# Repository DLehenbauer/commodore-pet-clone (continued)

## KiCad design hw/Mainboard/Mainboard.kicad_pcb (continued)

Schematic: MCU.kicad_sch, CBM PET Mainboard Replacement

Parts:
C68, C69, C81: 2.2u 6.3V; C_0402_1005Metric; LCSC C12530
C70, C71, C72, C73, C74, C75, C76, C77: 100n; C_0402_1005Metric; LCSC C307331
C78, C79: 30p; C_0402_1005Metric; LCSC C1570
C80: 10u; C_0603_1608Metric; LCSC C96446
D14: LED_GRN; LED_0603_1608Metric; LCSC C72043
J22: MENU; PinHeader_1x02_P2.54mm_Vertical; MOUSER 649-1012937893602BLF
JP8: DVI_CEC; SolderJumper-2_P1.3mm_Open_RoundedPad1.0x1.5mm
JP9: DVI_SDA; SolderJumper-3_P1.3mm_Open_RoundedPad1.0x1.5mm
JP10: DVI_SCL; SolderJumper-3_P1.3mm_Open_RoundedPad1.0x1.5mm
PT47, PT48: PowerTie_2; NetTie-2_SMD_Pad_1.6_to_0.4mm
R38, R39: 27; R_0603_1608Metric; LCSC C25190
R40, R41, R52, R53: 2k2; R_0402_1005Metric; LCSC C25879
R42, R43, R44, R45, R46, R47, R48: 33; R_0402_1005Metric; LCSC C25105
R49, R51, R55: 1k; R_0402_1005Metric; LCSC C11702
R50: 15k; R_0402_1005Metric; LCSC C25756
R54: 10k; R_0402_1005Metric; LCSC C25744
SW4: RUN; SW-TH_L6.0-W3.5-P6.50; MOUSER 611-PTS636SK43LFS
SW5: MENU; APEM_MJTP1117; MOUSER 642-MJTP1117
U21: RP2040; LQFN-56_L7.0-W7.0-P0.4-EP; LCSC C2040
Y1: 12 MHz; Crystal_SMD_3225-4Pin_3.2x2.5mm; LCSC C9002

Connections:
+3V3: PT47.1, R40.1, R41.1, R50.1, R52.1, R53.1; also elsewhere on the board
/MAGIC/FPGA/CEC: JP8.1 (A), U21.36 (GPIO24); also elsewhere on the board
/MAGIC/FPGA/FPGA_CLK: R48.1; also elsewhere on the board
/MAGIC/FPGA/I2C0_SCL: JP10.1 (A), R53.2; also elsewhere on the board
/MAGIC/FPGA/I2C0_SDA: JP9.1 (A), R52.2; also elsewhere on the board
/MAGIC/FPGA/I2C1_SCL: R41.2, U21.5 (GPIO3); also elsewhere on the board
/MAGIC/FPGA/I2C1_SDA: R40.2, U21.4 (GPIO2); also elsewhere on the board
/MAGIC/FPGA/SPI0_RX: U21.6 (GPIO4); also elsewhere on the board
/MAGIC/FPGA/SPI0_SCK: R43.1; also elsewhere on the board
/MAGIC/FPGA/SPI0_TX: R44.1; also elsewhere on the board
/MAGIC/FPGA/SPI0_~CS: R42.1; also elsewhere on the board
/MAGIC/FPGA/SPI1_RX: U21.15 (GPIO12); also elsewhere on the board
/MAGIC/FPGA/SPI1_SCK: R47.1; also elsewhere on the board
/MAGIC/FPGA/SPI1_TX: R45.1; also elsewhere on the board
/MAGIC/FPGA/SPI1_~CS: R46.1; also elsewhere on the board
/MAGIC/FPGA/SPI1_~READY: U21.13 (GPIO10); also elsewhere on the board
/MAGIC/FPGA/SWCLK: U21.24 (SWCLK); also elsewhere on the board
/MAGIC/FPGA/SWD: U21.25 (SWD); also elsewhere on the board
/MAGIC/FPGA/UART_RX: U21.3 (GPIO1); also elsewhere on the board
/MAGIC/FPGA/UART_TX: U21.2 (GPIO0); also elsewhere on the board
/MAGIC/FPGA/~CRESET: R54.2; also elsewhere on the board
/MAGIC/FPGA/~SPI_ENA: R50.2, R51.2, U21.26 (RUN); also elsewhere on the board
/MAGIC/MCU/DVDD: C68.1, C70.1, C71.1, U21.23 (DVDD), U21.45 (VREG_VOUT), U21.50 (DVDD)
/MAGIC/MCU/DVI/CEC: JP8.2 (B); also elsewhere on the board
/MAGIC/MCU/DVI/DVI_CK+: U21.28 (GPIO17); also elsewhere on the board
/MAGIC/MCU/DVI/DVI_CK-: U21.27 (GPIO16); also elsewhere on the board
/MAGIC/MCU/DVI/DVI_D0+: U21.30 (GPIO19); also elsewhere on the board
/MAGIC/MCU/DVI/DVI_D0-: U21.29 (GPIO18); also elsewhere on the board
/MAGIC/MCU/DVI/DVI_D1+: U21.32 (GPIO21); also elsewhere on the board
/MAGIC/MCU/DVI/DVI_D1-: U21.31 (GPIO20); also elsewhere on the board
/MAGIC/MCU/DVI/DVI_D2+: U21.35 (GPIO23); also elsewhere on the board
/MAGIC/MCU/DVI/DVI_D2-: U21.34 (GPIO22); also elsewhere on the board
/MAGIC/MCU/DVI/SCL: JP10.3 (B); also elsewhere on the board
/MAGIC/MCU/DVI/SDA: JP9.3 (B); also elsewhere on the board
/MAGIC/MCU/Flash/SCK: U21.52 (QSPI_SCLK); also elsewhere on the board
/MAGIC/MCU/Flash/SD0: U21.53 (QSPI_SD0); also elsewhere on the board
/MAGIC/MCU/Flash/SD1: U21.55 (QSPI_SD1); also elsewhere on the board
/MAGIC/MCU/Flash/SD2: U21.54 (QSPI_SD2); also elsewhere on the board
/MAGIC/MCU/Flash/SD3: U21.51 (QSPI_SD3); also elsewhere on the board
/MAGIC/MCU/Flash/~CS: U21.56 (QSPI_SS); also elsewhere on the board
/MAGIC/MCU/GP25: R55.1, U21.37 (GPIO25)
/MAGIC/MCU/GP27: C81.1, J22.2, SW5.2, U21.39 (GPIO27_ADC1)
/MAGIC/MCU/MCU_FPGA_CLK: R48.2, U21.18 (GPIO15)
/MAGIC/MCU/MCU_I2C0_SCL: JP10.2 (C), U21.41 (GPIO29_ADC3)
/MAGIC/MCU/MCU_I2C0_SDA: JP9.2 (C), U21.40 (GPIO28_ADC2)
/MAGIC/MCU/MCU_SPI0_SCK: R43.2, U21.8 (GPIO6)
/MAGIC/MCU/MCU_SPI0_TX: R44.2, U21.9 (GPIO7)
/MAGIC/MCU/MCU_SPI0_~CS: R42.2, U21.7 (GPIO5)
/MAGIC/MCU/MCU_SPI1_SCK: R47.2, U21.17 (GPIO14)
/MAGIC/MCU/MCU_SPI1_TX: R45.2, U21.14 (GPIO11)
/MAGIC/MCU/MCU_SPI1_~CS: R46.2, U21.16 (GPIO13)
/MAGIC/MCU/MCU_TESTEN: PT48.2, U21.19 (TESTEN)
/MAGIC/MCU/MCU_USB_D+: R38.1, U21.47 (USB_DP)
/MAGIC/MCU/MCU_USB_D-: R39.1, U21.46 (USB_DM)
/MAGIC/MCU/MCU_~CRESET: R54.1, U21.38 (GPIO26_ADC0)
/MAGIC/MCU/SD_DETECT: U21.11 (GPIO8); also elsewhere on the board
/MAGIC/MCU/SD_~CS: U21.12 (GPIO9); also elsewhere on the board
/MAGIC/MCU/USB/USB_D+: R38.2; also elsewhere on the board
/MAGIC/MCU/USB/USB_D-: R39.2; also elsewhere on the board
/MAGIC/MCU/XIN: C78.2, U21.20 (XIN), Y1.1
/MAGIC/MCU/XOUT: R49.2, U21.21 (XOUT)
GND: C68.2, C69.2, C70.2, C71.2, C72.2, C73.2, C74.2, C75.2, C76.2, C77.2, C78.1, C79.1, C80.2, C81.2, D14.1 (K), J22.1, PT48.1, SW5.1, U21.57 (GND), Y1.2, Y1.4; also elsewhere on the board
MCU_IOVDD: C69.1, C72.1, C73.1, C74.1, C75.1, C76.1, C77.1, PT47.2, U21.1 (IOVDD), U21.10 (IOVDD), U21.22 (IOVDD), U21.33 (IOVDD), U21.42 (IOVDD), U21.43 (ADC_AVDD), U21.44 (VREG_IN), U21.48 (USB_VDD), U21.49 (IOVDD)
unnamed: C79.2, R49.1, Y1.3
unnamed: C80.1, R51.1, SW4.2
unnamed: D14.2 (A), R55.2
PD_GND: SW4.1; also elsewhere on the board

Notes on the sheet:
IO/USB/AVDD Decoupling
~{SPI_ENA} is driven low during FPGA programming. We use this to hold the MCU in reset when updating the FPGA to avoid contention on SPI pins. FT2232H can source/sink ~8ma, so 1K should be ok.
DVDD Decoupling
10k resistor on ~{CRESET} enables programmer to override MCU during development.

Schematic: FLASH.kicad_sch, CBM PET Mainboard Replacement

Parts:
C85: 100n; C_0402_1005Metric; LCSC C307331
R72: 10k; R_0402_1005Metric; LCSC C25744
R73: 1k; R_0402_1005Metric; LCSC C11702
SW6: BOOTSEL; SW-TH_L6.0-W3.5-P6.50; MOUSER 611-PTS636SK43LFS
U22: W25Q128JVS; SOIC-8_5.23x5.23mm_P1.27mm; LCSC C97521

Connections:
+3V3: C85.1, R72.1, U22.8 (VCC); also elsewhere on the board
/MAGIC/MCU/Flash/SCK: U22.6 (CLK); also elsewhere on the board
/MAGIC/MCU/Flash/SD0: U22.5 (DI(IO0)); also elsewhere on the board
/MAGIC/MCU/Flash/SD1: U22.2 (DO(IO1)); also elsewhere on the board
/MAGIC/MCU/Flash/SD2: U22.3 (IO2); also elsewhere on the board
/MAGIC/MCU/Flash/SD3: U22.7 (IO3); also elsewhere on the board
/MAGIC/MCU/Flash/~CS: R72.2, R73.2, U22.1 (~CS); also elsewhere on the board
GND: C85.2, SW6.1, U22.4 (GND); also elsewhere on the board
unnamed: R73.1, SW6.2

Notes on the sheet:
Flash

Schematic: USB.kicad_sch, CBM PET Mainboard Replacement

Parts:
C84: 4.7u 16V; C_0603_1608Metric; LCSC C19666
J25: USB2.0_HOST_TYPE_C; USB-C_SMD-TYPE-C-31-M-12; LCSC C165948
PT51, PT52, PT53, PT54: PowerTie_2; NetTie-2_SMD_Pad_1.6_to_0.4mm
R70, R71: 56k; R_0402_1005Metric; LCSC C25796

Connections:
+5V: C84.1, PT51.1, PT52.1; also elsewhere on the board
/MAGIC/MCU/USB/CC1: J25.A5 (CC1), R70.2
/MAGIC/MCU/USB/CC2: J25.B5 (CC2), R71.2
/MAGIC/MCU/USB/USB_D+: J25.A6 (D+), J25.B6 (D+); also elsewhere on the board
/MAGIC/MCU/USB/USB_D-: J25.A7 (D-), J25.B7 (D-); also elsewhere on the board
/MAGIC/MCU/USB/VBUS1: J25.A4_B9 (VBUS), PT51.2, R70.1
/MAGIC/MCU/USB/VBUS2: J25.A9_B4 (VBUS), PT52.2, R71.1
GND: J25.S1 (SHIELD); also elsewhere on the board
unnamed: J25.A1_B12 (GND), PT54.2
unnamed: J25.A12_B1 (GND), PT53.2
PD_GND: C84.2, PT53.1, PT54.1; also elsewhere on the board

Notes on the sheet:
USB 2.0 Host over USB-C connector The 56k pullups on CC1 and CC2 identify as a downstream facing port supplying 5V @ 900ma.

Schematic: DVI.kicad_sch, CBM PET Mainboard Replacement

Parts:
J23: NOT_HDMI_A; HDMI_A_Molex_208658-1001_Horizontal; LCSC C138388
PT49, PT50: PowerTie_2; NetTie-2_SMD_Pad_1.6_to_0.4mm
R56, R57, R58, R59, R60, R61, R65, R66, R67: 270; R_0603_1608Metric; LCSC C22966
R62, R63, R64: 2k2; R_0402_1005Metric; LCSC C25879

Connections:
+3V3: R62.1; also elsewhere on the board
+5V: PT49.1; also elsewhere on the board
/MAGIC/MCU/DVI/CEC: R62.2, R67.1; also elsewhere on the board
/MAGIC/MCU/DVI/DVI_CK+: R65.1; also elsewhere on the board
/MAGIC/MCU/DVI/DVI_CK-: R66.1; also elsewhere on the board
/MAGIC/MCU/DVI/DVI_D0+: R60.1; also elsewhere on the board
/MAGIC/MCU/DVI/DVI_D0-: R61.1; also elsewhere on the board
/MAGIC/MCU/DVI/DVI_D1+: R58.1; also elsewhere on the board
/MAGIC/MCU/DVI/DVI_D1-: R59.1; also elsewhere on the board
/MAGIC/MCU/DVI/DVI_D2+: R56.1; also elsewhere on the board
/MAGIC/MCU/DVI/DVI_D2-: R57.1; also elsewhere on the board
/MAGIC/MCU/DVI/HDMI_CEC: J23.13 (CEC), R67.2
/MAGIC/MCU/DVI/HDMI_CK+: J23.10 (CK+), R65.2
/MAGIC/MCU/DVI/HDMI_CK-: J23.12 (CK-), R66.2
/MAGIC/MCU/DVI/HDMI_D0+: J23.7 (D0+), R60.2
/MAGIC/MCU/DVI/HDMI_D0-: J23.9 (D0-), R61.2
/MAGIC/MCU/DVI/HDMI_D1+: J23.4 (D1+), R58.2
/MAGIC/MCU/DVI/HDMI_D1-: J23.6 (D1-), R59.2
/MAGIC/MCU/DVI/HDMI_D2+: J23.1 (D2+), R56.2
/MAGIC/MCU/DVI/HDMI_D2-: J23.3 (D2-), R57.2
/MAGIC/MCU/DVI/SCL: J23.15 (SCL), R63.2; also elsewhere on the board
/MAGIC/MCU/DVI/SDA: J23.16 (SDA), R64.2; also elsewhere on the board
/MAGIC/MCU/DVI/VCC: J23.18 (+5V), PT49.2, R63.1, R64.1
/MAGIC/MCU/DVI/VSS: J23.2 (D2S), J23.5 (D1S), J23.8 (D0S), J23.11 (CKS), J23.17 (GND), PT50.2
PD_GND: J23.SH, PT50.1; also elsewhere on the board

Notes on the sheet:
NOT
CEC and I2C are for possible future use. DANGER: Closing the SCL/SDA jumpers pulls the corresponding GPIO pins to +5V. Only do this if you know what you're doing.

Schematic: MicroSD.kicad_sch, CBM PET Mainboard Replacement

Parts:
C82: 100n; C_0402_1005Metric; LCSC C307331
C83: 10u 6.3V; C_0402_1005Metric; LCSC C15525
J24: MicroSD; TF-SMD_TF-PUSH; LCSC C393941
R68: 10k; R_0402_1005Metric; LCSC C25744
R69: 33; R_0402_1005Metric; LCSC C25105
RN16: 10k; R_Array_Convex_4x0603; LCSC C29718

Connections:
+3V3: C82.1, C83.1, J24.4 (VDD), R68.1, RN16.5 (R4.2), RN16.6 (R3.2), RN16.7 (R2.2), RN16.8 (R1.2); also elsewhere on the board
/MAGIC/FPGA/SPI1_RX: R69.2; also elsewhere on the board
/MAGIC/FPGA/SPI1_SCK: J24.5 (CLK); also elsewhere on the board
/MAGIC/FPGA/SPI1_TX: J24.3 (CMD), RN16.3 (R3.1); also elsewhere on the board
/MAGIC/MCU/SD_DETECT: J24.9 (DET); also elsewhere on the board
/MAGIC/MCU/SD_~CS: J24.2 (DAT3/CD), RN16.2 (R2.1); also elsewhere on the board
GND: C82.2, C83.2, J24.6 (VSS), J24.10 (SHIELD), J24.11 (SHIELD), J24.12 (SHIELD), J24.13 (SHIELD); also elsewhere on the board
unnamed: J24.1 (DAT2), RN16.1 (R1.1)
unnamed: J24.7 (DAT0), R69.1, RN16.4 (R4.1)
unnamed: J24.8 (DAT1), R68.2

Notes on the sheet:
DAT[0] : (POCI) is open-drain output that requires pullup. DAT[2:1] : Unused inputs in SPI mode. Pullups recommended to avoid current draw due to metastablitiy. DAT[3] : (~{CS}) has built-in 22-50k pullup to ensure card is deselected by default. CMD : (PICO) input in SPI mode. CLK : (SCK) always an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
MicroSD

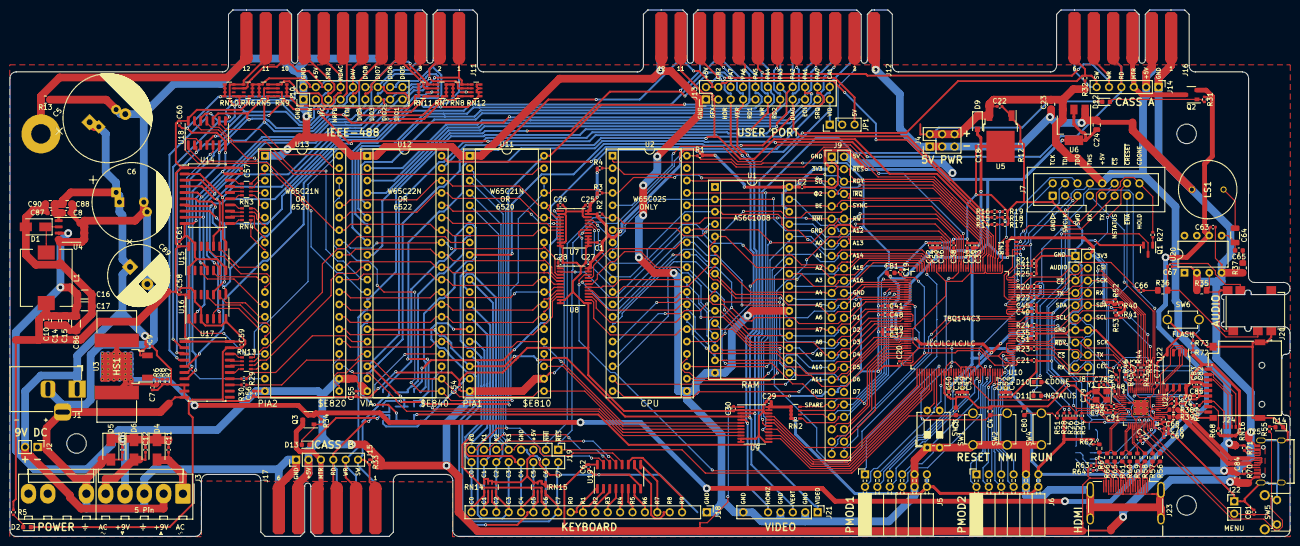
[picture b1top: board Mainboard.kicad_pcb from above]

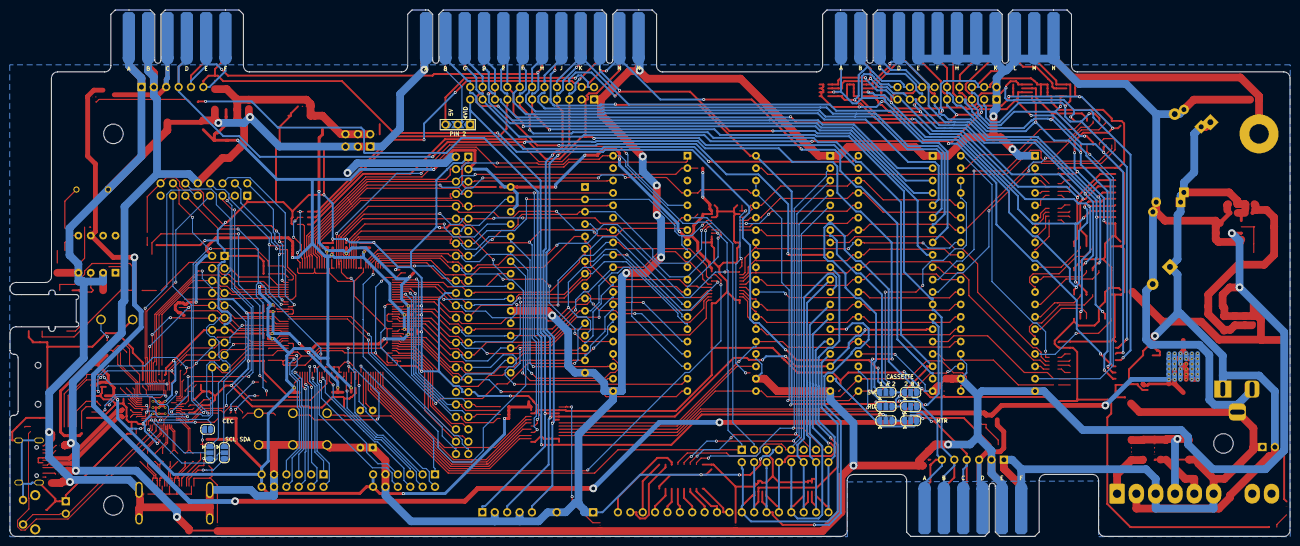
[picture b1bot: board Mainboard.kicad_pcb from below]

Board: 2 copper layers, 262.5 x 107.9 mm, 313 parts (14 on the bottom side), 372 nets.

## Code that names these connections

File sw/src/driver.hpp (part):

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        static const CGpioPins</* start: */ 5, /* count: */ 15> a0to14Pins;
        static const CGpioPins</* start: */ 20, /* count: */ 8> dataPins;

        // rwb  = gpio0
        // a15  = gpio1
        // pend = gpio2
        // done = gpio3
        // clk  = gpio4
        // a0   = gpio5
        // a1   = gpio6
        // a2   = gpio7
        // a3   = gpio8
        // a4   = gpio9  (MISO)
        // a5   = gpio10 (MOSI)
        // a6   = gpio11 (SCLK)
        // a7   = gpio12
        // a8   = gpio13
        // a9   = gpio14 (TXD)
        // a10  = gpio15 (RXD)
        // a11  = gpio16
        // a12  = gpio17
        // a13  = gpio18
        // a14  = gpio19
        // d0   = gpio20
        // d1   = gpio21
        // d2   = gpio22
        // d3   = gpio23
        // d4   = gpio24
        // d5   = gpio25
        // d6   = gpio26
        // d7   = gpio27

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
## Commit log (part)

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2022-09-29 wip: pico tweaks
2022-10-01 fw: usb kbd via TinyUSB
2022-10-01 README.md
2022-10-01 wip: crtc
2022-10-01 rtl: break out crtc values
2022-10-02 spi: rename states
2022-10-02 spi: use 0x84 for 'write_at()'
2022-10-02 rtl: spi read wip
2022-10-04 wip: edge_detect
2022-10-08 vscode: explicitly use 'root' user in dev container
2022-10-08 vscode: do not detect indentation
2022-10-11 wip: restore read_next
2022-10-11 wip: avoid using byte_valid as clk
2022-10-12 wip: hang on read
2022-10-13 wip: spi with always_comb
2022-10-14 _comb -> single _ff
2022-10-14 wip: better results w/o cs_n
2022-10-15 Capture tx on pi_done_in
2022-10-15 fw: boots w/spi, but no keyboard?
2022-10-16 display video hack
2022-10-17 vscode: Add PicoDVI to launch.json
2022-10-19 fw: 720x480p
2022-10-26 rtl: improve typing of crtc
2022-10-27 fw: Use 8 MHz SPI
2022-10-31 docs: video.md
2022-11-02 spi working @ 8 MHz
2022-11-06 video docs
2022-11-06 whitespace
2022-11-06 crtc: missing bit in R12
2022-11-08 wip: partial display start plumbing
2022-11-08 video: remove unused first_o
2022-11-08 video: separate pixel_ctr
2022-11-08 video: lift pixel counter out of h_sync, blanking is back
2022-11-09 video: wip row/col ctr
2022-11-09 video: use ma_i for character address, ra_i doesn't work, sometimes screen is not centered.
2022-11-09 video: remove unused row/char_addr
2022-11-10 Fix a couple benign warnings
2022-11-12 video: Fix _d / _q typo
2022-11-12 video: use _ff for last_* signals
2022-11-15 top: rename signals
2022-11-16 top: pi_data -> debug_o
2022-11-16 move spi into main, video garbled
2022-11-16 move timing and pi_ctl to separate files
2022-11-16 main.sv: rename module signals
2022-11-16 stub main_tb
2022-11-17 fw: Merge PENDING_B and SPI_CSN
2022-11-17 rtl: Merge spi_pending_ni and spi_cs_ni
2022-11-18 rtl: move debug_o decl
2022-11-18 rtl: rename and simplify spi
2022-11-18 rtl: rename spi_bridge
2022-11-18 rtl: fix tb_spi.sv
2022-11-22 rtl: fix tb_spi_bridge.sv
2022-11-22 rtl: tweak spi_bridge
2022-11-22 fw: tweak spi_bridge
2022-11-23 rtl: rename to spi_pending_out
2022-11-23 rtl: spi_done -> spi_ready
2022-11-23 rtl: improve spi_bridge
2022-11-23 rtl: remove reset alias from spi_bridge
2022-11-24 rtl: move spi_ready_no negation into spi_bridge
2022-11-24 fw: move spi to driver.c
2022-11-24 Revert "rtl: move spi_ready_no negation into spi_bridge"
    This reverts commit 6c3ece49607a4107aeb7ab5cf6bbce34afeb89f2.
2022-11-24 fw: rm unused 'cmd_rw_n' from spi_bridge
2022-11-24 fw: make 'video_char_buffer' global
2022-11-24 fw: factor 'pet.c' from 'main.c'
2022-11-24 fw: spi_read/write matches memcpy arg order
2022-11-24 rtl: use 'spi_enable' for control.sv
2022-11-24 rtl: diagram in bus.sv
2022-11-25 rtl: new timing wip
2022-11-26 fw: rm cpu_res_b pin
2022-11-26 rtl: generating clk_cpu / phi2 from timing2
2022-11-26 rtl: comment
2022-11-26 fw: factor spi_bridge_driver
2022-11-26 rtl: move to spi_driver.sv
2022-11-27 rtl: introduce 'spi_wr_en'
2022-11-27 rtl: kbd using new clks
2022-11-27 rtl: cpu_sel/en gated on cpu_ready
2022-11-27 rtl: remove unused old timing signals
2022-11-27 rtl: replace pi_read/write with spi_rd/wr_en
2022-11-27 rtl: generate spi_ready_o from new timing
2022-11-27 rtl: remove old cpu_enable and cpu_read
2022-11-27 rtl: rm old timing
2022-11-27 rtl: fix dual-clock ram
2022-11-27 rtl: no violations @ 4 MHz SPI
2022-11-27 fw: 4 MHz SPI
2022-11-28 rtl: fix lower-case (use clk8n to capture spi)
2022-11-28 rtl: timing2.sv -> timing.sv
2022-11-29 rtl: sdc tweaks
2022-11-30 rtl: update conventions in address_decoding.sv
2022-11-30 rtl: update tb_crtc.sv
2022-11-30 rtl: sdc wip
2022-12-01 docs: add kicad plugins to tools.md
2022-12-13 docs: todo.md
2022-12-13 spi constraints
2022-12-14 rtl: more constraints
2022-12-15 docs: add PCB fabrication
2022-12-16 doc: add SMD SRAM to datasheets.md
2022-12-16 docs
2022-12-16 Add 'no-OS-FatFS-SD-SPI-RPi-Pico' submodule
2022-12-16 hw: fix disconnection in schematic
2022-12-22 rtl: last working config
2022-12-22 Move schematics to separate repo
2022-12-22 Fix ram_ce for LKG
2022-12-23 rtl: Set spi_tx to high-z when CS is deasserted
2022-12-23 docs: Add JRE to tools.md
2022-12-26 hw: whitespace
2022-12-26 docs: Add via size calculator
2022-12-26 rtl: add workaround for RAM adapter (disabled)
2022-12-28 hw: T8 (wip)
2023-01-01 docs: Move T8 docs to t8.md
2023-01-04 fw: faux-pi-0, memory test, init_sd conflicts w/IRQ
2023-01-04 hw: routed, but trace sizes need to be reviewed/fixed
2023-01-07 docs: Add rp2040 to datasheets
2023-01-08 rtl: remove use of ram_ce
2023-01-08 hw: wip
2023-01-09 rtl: move quartus project to ep2
2023-01-09 rtl: breakout 'inout' at main.sv to _i, _o, _oe
2023-01-09 rtl: stubbed 'top.sv' for T8
2023-01-09 hw: pull cbus0 high
2023-01-15 hw: larger schematic pages, routed w/netties
2023-01-16 hw: indent copper fill
2023-01-21 jlcpcb - 1/19
2023-01-23 rtl: add PET.chain.xml
2023-01-23 hw: drive CRESET through 10k, remove TDO pullup
2023-01-23 hw: 10uF -> 22uF smoothing caps
2023-01-23 rtl: declare T8 interface pins
2023-01-29 hw: minor routing tweaks
2023-01-29 rtl: fix T8 signal names in interface
2023-02-04 rtl: drive 'status_no'
2023-02-04 fw: suspend CPU during RAM test
2023-02-05 fw: comment
2023-02-05 fw: main.c should include test.h
2023-02-06 hw: pin 1 of 50 MHz oscillator can float
2023-02-06 hw: touchup routing & silk
2023-02-11 rtl: add 'sim.bat'
2023-02-18 rtl: add main.sv, reorder signals, fix _oe polarity
2023-02-18 rtl: move design to src/ subfolder
2023-02-19 rtl: 'top_driver' and 'mock_cpu'
2023-02-20 git: add jtag.log to .gitignore
2023-02-21 wip: fw: headers & comments
2023-02-22 wip: fw: comments in roms/CMakeLists.txt
2023-02-22 wip: update build/setup scripts to build fw/ instead of sw/
2023-02-22 wip: fw: target Pico SDK 1.5 (rm 'rpi' from docker)
2023-02-22 wip: sw: remove
2023-02-23 rtl: .gitignore efinity dbg artifacts
2023-02-23 rtl: spi1 echos received byte
2023-02-25 TODO.md
2023-02-25 rtl: add generated (unconstrained) SDC
2023-02-25 rtl: sdc for spi1 (wip)
2023-02-26 rtl: SDC for SPI1
2023-02-26 rtl: use active high for most signals
2023-02-26 rtl: fix 'spi_rw_no' initialization (VERI-2522)
2023-02-26 rtl: connect spi1 (wip)
2023-03-01 sim.bat: add '--view' helper
2023-03-04 fw: ram test addr_max should be 0xffff
2023-03-04 rtl: passed ram tests
2023-03-05 fw: add iteration count to RAM test
2023-03-05 rtl: Introduce 'cpu_en', drive 'cpu_be' and 'cpu_clk'
2023-03-06 hw: correct /RD and /WR labels
2023-03-06 rtl: add control for RES_B and RDY
2023-03-08 rtl: rename clocks to 'setup_clk' and 'strobe_clk'
2023-03-09 rtl/sim: dumpvars(0, sim);
2023-03-09 rtl: add IO chips, missing vblank and read back of gfx/business mode
2023-03-09 rtl: placeholder video generator for vblank
2023-03-11 rtl: add keyboard and audio
2023-03-11 fw: roms.h
2023-03-12 sim.bat: do not run vpp if iverilog returns error
2023-03-12 rtl: video (wip)
2023-03-12 rtl: dotgen (todo: adjust not yet correct)
2023-03-15 rtl: CRTC / First working video
2023-03-16 rtl: flatten CRTC implementation
2023-03-17 rtl: 'CRTC.ma' should increment until end of 'h_total'
2023-03-18 rtl: video end of frame, gfx, no_row
2023-03-18 rtl: factor crtc_driver for use in video_tb (wip)
2023-03-18 rtl: 80 columns
2023-03-19 fw: config fpga
2023-03-19 fw: move FPGA clock config to fpga.c
2023-03-19 fw: factor 'fpga_config' into separate function
2023-03-19 rtl: add 'col_80_mode' to toggle 40/80 colums
2023-03-20 hw: rename 'CPLD' sheet to 'FPGA'
2023-03-20 hw: remove 50 MHz oscillator
2023-03-20 hw: use LM317 for +5V
2023-03-22 hw: tidy power and resize pages
2023-03-22 hw: tidy CPU, rename RD/WR strobe to RAM_OE/_WE, debounce switches
2023-03-22 hw: tidy IO, move CPU decoupling caps
2023-03-23 hw: tidy audio, cass, IEEE, keyboard, magic, user
2023-03-23 hw: tidy cass more
2023-03-25 hw: comments
2023-03-25 doc: add block diagram
2023-03-25 doc: remove extra arrow from block diagram
2023-03-26 doc: update memory map for bank switching
2023-03-26 hw: replace ram_ce with ram_a15
2023-03-27 hw: tidy MCU and a few missed PD_
2023-03-27 hw: move microSD to it's own sheet
2023-03-28 hw: move usb to it's own sheet
2023-03-28 hw: move flash to separate sheet
2023-03-29 hw: Use 74HC154 for keyboard
2023-04-16 docs: remove timing.md (same info is in video.md)
2023-04-17 Fix typos
2023-04-27 rtl: add 'audio_no'
2023-05-06 wip: keyboard ex header
2023-05-13 hw: autoroute
2023-05-13 wip: rtl: add DLehenbauer/icesid
2023-05-13 fw: embed fpga bitstream
2023-05-15 Add SID at $8F00
2023-05-15 Init uart after setting clk_sys
2023-05-15 Update icesid submodule
2023-05-18 hw: update 10u caps
2023-05-24 rtl: sid (wip)
2023-07-04 hw: routing / silk wip
2023-07-04 hw: minor cleanup
2023-07-15 hw: unstitched copper fills
2023-07-16 hw: stitched copper planes (wip)
2023-07-16 hw: heat sink, trace size, more stitching
2023-07-20 HW: Remove 'MANUFACTURER' and 'MAXIMUM_PACKAGE_HEIGHT' cols from BOM
2023-07-20 HW: Rename 'MFR' to 'MPN' in BOM
2023-07-21 hw: add more Mouse part numbers
2023-07-21 hw: PN for IC, remove dup PNs, remove redundant headroom text on PWR
2023-07-22 hw: silkscreen, no pcb changes
2023-07-24 hw: move GND via under user port pin 1
2023-07-24 hw: touch up +1V2, +3V3 regulator layout
2023-07-26 docs: link to ROM hash codes
2023-07-28 hw: thermal vias, whitespace, refill
2023-07-28 hw: fix spi1 rx/tx pins
2023-07-28 fw: skip I/O ranges in memory test
2023-07-28 hw: rotate regulator 90 degrees
2023-07-30 hw: 9V DC plug on left edge, change default track size
2023-08-01 doc: PMOD reference
2023-08-02 hw: move hdmi connector
2023-08-03 hw: PMOD footprint
2023-08-07 hw: 25x2 header (wip)
2023-08-08 hw: 2x config switch (wip)
2023-08-13 hw: add flexible heat sink footprint
2023-08-13 hw: remove vp/ml pins
2023-08-15 hw: routing (wip)
2023-08-17 hw: header_and_jumper, button for flashing (wip)
2023-08-21 hw: revert to single gnd plane
2023-08-21 rtl: document 'status_no'
2023-08-22 rtl: simplify cpu_res_i
2023-08-22 hw: fix sim
2023-08-24 rtl: update sim.bat for efinity 2023.1
2023-08-24 hw: minor schematic update
2023-08-26 rtl: cdc for SPI @ 16 MHz (npa garbled, b2p hang during load)
2023-08-26 hw: rotate buck converter (wip)
2023-08-28 hw: remove series termination, gnd under hdmi (wip)
2023-08-28 gw: empty dir, remove icesid (wip)
2023-08-29 gw: timing (wip)
2023-08-30 hw: fill, routing, and silk touchups (wip)
2023-09-01 hw: gnd around fpga_clk, 10u caps on 3v3 (wip)
2023-09-01 doc: add Freescale style guide
2023-09-01 gw: make rdy bidirectional, add empty main.sv
2023-09-03 hw: touch ups / avoid a few uniques (wip)
2023-09-03 rtl: rm icesid, spi w/clk16 again (wip)
2023-09-03 rtl: generate 16 MHz clk
2023-09-05 gw: simple spi echo (16 MHz with 180 MHz sys_clk_i)
2023-09-06 gw: simple spi echo (24 MHz with 64 MHz sys_clk_i)
2023-09-07 hw: routing touchups (wip)
2023-09-07 gw: stub FSM advancing on 24 MHz SCK
2023-09-13 doc: notes on T8 bram
2023-09-13 gw: spi1 protocol (wip)
2023-09-20 hw: touchups (wip)
2023-09-21 hw: config silk
2023-09-24 gw: convert spi1 to wishbone/sba (wip)
2023-09-24 gw: add 'sim.sh'
2023-09-26 gw: use fifo for expected in spi1_tb (wip)
2023-09-26 gw: use clk_i to wait for edge detection in _tb
2023-10-01 hw: caps & logos (wip)
2023-10-01 gw: spi1_tb
2023-10-02 hw: remove net/power ties
2023-10-03 hw: renumber rn. tidy fpga schematics
2023-10-04 hw: review LCSC parts
2023-10-07 hw: before stitching
2023-10-14 hw: thermal vias & more stitching
2023-10-14 hw: stitching
2023-10-28 hw: add hatching to PET power connector
2023-10-28 hw: PS schmematic notes
2023-10-28 hw: tidy stitching (wip)
2023-11-04 hw: tidy vias & silk (wip)
2023-11-04 hw: tidy
2023-11-05 hw: original prod
2023-11-06 hw: consistent resistor notation
2023-11-06 hw: remove hand assembled parts
2023-11-07 hw: fix cpl
2023-11-08 hw: add pmod and dip switch to BOM
2023-11-09 hw: rotate U10 90 degrees in positions.csv
2023-11-09 hw: 3d model for barrel jack connector
2023-11-15 rtl: peri.xml for Rev A
2023-11-16 fw: print spi1 baudrate on start
2023-11-16 fw: bitstream from rev A
2023-11-16 fw: sd build fix
2023-11-23 fw(rev-b): light LED during configuration
2024-05-25 Update README.md
    Link to manufacturing files.
2024-09-14 gw: Efinity 2024.1.163 and remove PET.peri.new.xml
